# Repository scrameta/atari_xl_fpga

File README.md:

# atari_xl_fpga

An FPGA implementation of the Atari 800XL (and, with a swapped memory map, the
Atari 5200), ported to a wide range of FPGA boards. The shared core, ZPU and
common building blocks live in a separate repository,
[**atari_xl_fpga_common**](https://github.com/scrameta/atari_xl_fpga_common),
included here as a git submodule at `common/`. This repository provides the
per-board top levels, the standalone Atari chip replacements, and the firmware.

The project also grew a companion set of individual chip replacements (POKEY,
GTIA, ANTIC, Sally/6502) — one of which, **PokeyMAX**, went on to become a
product in its own right.

> This repository was migrated from a long-lived SVN history, so some of the
> commit history and layout reflects that heritage.

## Contents

- [What this is](#what-this-is)
- [Getting the code](#getting-the-code)
- [Repository layout](#repository-layout)
- [The core](#the-core)
- [Supported boards](#supported-boards)
- [Individual chip replacements](#individual-chip-replacements)
- [Downstream forks](#downstream-forks)
- [Related work](#related-work)
- [Firmware](#firmware)
- [Toolchain](#toolchain)
- [Building](#building)
- [Licensing](#licensing)
- [Credits and references](#credits-and-references)

## What this is

The project started as an Atari 800XL built on a Terasic **DE1** (Cyclone II).
Because the Atari 5200 shares most of the 800XL hardware and differs mainly in
its memory map and I/O, a 5200 variant fell out fairly naturally and is
maintained alongside the 800XL builds.

Beyond raw machine emulation, a **ZPU** soft-core provides the "glue" a real
setup needs: SIO disk-drive emulation, menu/UI, timers and similar. The ZPU and
core themselves live in the shared
[atari_xl_fpga_common](https://github.com/scrameta/atari_xl_fpga_common) repo;
the board-specific firmware builds live here in the `firmware_*` folders.

Over time the core was ported to many different FPGA boards, and separately the
individual custom Atari ICs were reimplemented as standalone RTL so they could
be dropped into real machines.

## Getting the code

The shared core is a submodule, so clone recursively:

```sh
git clone --recursive https://github.com/scrameta/atari_xl_fpga

# …or, if you already cloned without --recursive:
git submodule update --init --recursive
```

The core then appears under `common/`. To move onto a newer core revision, bump
the submodule pointer (see the
[common repo](https://github.com/scrameta/atari_xl_fpga_common#using-this-repository)
for the exact commands).

## Repository layout

Everything lives under `atari_800xl/`.

| Path | Description |
| --- | --- |
| `common/` | **Submodule:** shared core, ZPU and components — see [atari_xl_fpga_common](https://github.com/scrameta/atari_xl_fpga_common). |
| `atari_chips/` | Standalone RTL for individual Atari ICs — see [below](#individual-chip-replacements). |
| `atari_chips/hardware/` | Board designs and Gerbers for the chip-replacement hardware. |
| *(one folder per board)* | Per-board top level, pin constraints, PLLs and build scripts — see [below](#supported-boards). |
| `firmware_*` | ZPU firmware builds (see [Firmware](#firmware)). |
| `VERSION` | Core version string. |
| `buildall.sh`, `package.pl`, `makemifall` | Top-level build / packaging helpers. |

## The core

The main core lives in the `common/` submodule
([atari_xl_fpga_common](https://github.com/scrameta/atari_xl_fpga_common)) and is
shared unchanged across every board port. Each board folder in this repository
is essentially a thin top level — clocking, pin mapping, memory controller,
board-specific I/O — wrapped around that common core.

The 5200 variants (`*_5200`) reuse the same core with the 5200 memory map and
I/O differences.

## Supported boards

Each board has its own top-level folder containing its constraints, PLL/clocking
and build script.

### Actively supported / working

| Board | Folder | Notes |
| --- | --- | --- |
| Terasic DE1 | `de1`, `de1_5200` | The original target (Cyclone II). |
| MCC216 | `mcc216`, `mcc216_5200` | Arcade / retro-gaming board. |
| MCCTV | `mcctv`, `mcctv_5200` | Arcade / retro-gaming board. |
| MIST | `mist`, `mist_5200` | |
| Turbo Chameleon (v1) | `chameleon` | |
| Turbo Chameleon 2 | `chameleon2` | |
| Vampire V4 | `vampire_v4sa_atari800xl` | Pinout worked out independently. |

(`mcc_common` holds shared MCC support code.)

### Experimental / community / incomplete

| Board | Folder | Status |
| --- | --- | --- |
| FPGA Arcade Replay | `replay` | Unfinished — fought the framework and the lack of SignalTap. |
| Terasic SoCKit | `sockit` | Unfinished — DDR3 IP proved troublesome. |
| Aeon Lite | `aeon_lite` | Community-contributed board; experimental. |
| Papilio DUO | `papilioduo` | Experimental. |
| eclaireXL ITX | `eclaireXL_ITX` | |

> **Vampire V4:** the pin assignments here were reverse-engineered / worked out
> independently rather than supplied by the vendor.

## Individual chip replacements

Separately from the full-machine core, `atari_chips/` contains standalone RTL
reimplementations of the individual Atari custom ICs, intended for dropping into
real hardware. `atari_chips/hardware/` holds the associated board designs and
Gerbers, and each chip has simulation scripts and testbenches
(`simulate_*max.sh`, `tb_*max/`).

| Chip | Folder(s) | Status |
| --- | --- | --- |
| **POKEY** (PokeyMAX) | `pokey`, `pokeyv2`, `pokey_digi` | **Works — matured into a full product.** Won the ABBUC hardware competition and is actively developed as PokeyMAX. |
| **GTIA** | `gtia` | Works well; used as the author's main GTIA. Developed and working prior to Sophia. |
| **Sally (6502)** | `sally` | Works, but sees little use; HALT timing is not fully verified. |
| **ANTIC** | `antic` | Incomplete — the DMA timing was never fully nailed down. |

There is also a `digimax` (DigiMAX-style DAC) in the same area.

If you're specifically after PokeyMAX rather than the FPGA computer, that work
has taken on a life of its own — see [64kib.com](https://www.64kib.com/) and the
[ABBUC](https://www.abbuc.de/) community.

## Downstream forks

- **[Atari800_MiSTer](https://github.com/MiSTer-devel/Atari800_MiSTer)** — the
  MiSTer port. It forked this project by copying the SVN repository and has
  broadly kept the core the same, while adding newer features of its own — for
  example VBXE and PokeyMAX support integrated into the full 800XL FPGA core.
  It's actively maintained by the MiSTer community and is a good place to look
  if you want a well-supported, feature-rich build on MiSTer hardware.

## Related work

- **[tonnere](https://github.com/scrameta/tonnere)** — Project Thunder
  (*tonnere* is French for thunder), the successor board to the EclaireXL
  (itself named for lightning), now being renamed **MegaXE**. An Atari XL/XE
  FPGA board carrying this lineage forward. It shares the same
  [common core](https://github.com/scrameta/atari_xl_fpga_common).
- **`ultimate_cart`** — Veronica, a separate 65816 upgrade project for the
  800XL (not a board port of this core).

## Firmware

The ZPU firmware provides the drive emulator, menu system and supporting
services. The ZPU core and services themselves live in the `common/` submodule;
these folders hold the board-specific firmware builds:

| Folder | Description |
| --- | --- |
| `firmware_eclairexl` | Firmware for the eclaireXL / newer targets. |
| `firmware_legacy` | Firmware for the older targets. |

The build flow compiles the firmware to a ZPU ROM that is embedded into the
core (`makemif*` / `zpu_rom.*` artefacts you'll see in the board folders).

## Toolchain

Which tool you need depends on the target FPGA:

- **Altera / Intel boards** — Quartus. In general the **latest** Quartus works,
  **except** for the older Cyclone parts, which were dropped from newer
  Quartus. For those use the newest version that still supports the device:
  - **Cyclone II** (e.g. DE1): last supported by **Quartus II 13.0sp1**.
  - **Cyclone III/IV**: last supported by **Quartus II 13.1**.
  - **MAX 10** and Cyclone 10 LP: use a modern Quartus (15.x or later).
- **Xilinx boards** (Papilio DUO, Aeon Lite, FPGA Arcade Replay) — **ISE**
  (project files: `*.prj`, `*.xst`, `*.ucf`, `*.ut`). Exact ISE version isn't
  recorded; a late ISE 14.x release is the usual choice for these Spartan-6-era
  parts.

Simulation of the core and sub-blocks lives in the `common/` submodule; the
chip replacements have their own testbenches under `atari_chips/tb_*` driven by
the `simulate_*.sh` scripts. A ZPU toolchain is required to (re)build the
firmware.

## Building

Make sure the `common/` submodule is populated first (see
[Getting the code](#getting-the-code)). Each board folder then contains a
`build.sh` (and often a `build.pl`) that drives the flow for that target.
`buildall.sh` at the top level builds across boards, and `makemifall` /
`package.pl` handle ROM/MIF generation and packaging.

> This is a large, long-lived hobby codebase migrated from SVN. Build scripts
> assume the author's environment in places; expect to adjust paths and tool
> versions for your setup.

## Licensing

**Please read this carefully — the licensing here is genuinely mixed and, in
places, unsettled.**

This project combines RTL and firmware from many sources, and the shared
`common/` submodule adds more of the same. The author does **not** own copyright
in all of it, so a single blanket open-source licence (GPL or otherwise)
**cannot** be applied to the whole tree. See the `COPYRIGHT_NOTICE` file here and
the one in [atari_xl_fpga_common](https://github.com/scrameta/atari_xl_fpga_common),
which aggregate the copyright notices for the various components — note they are
acknowledged to be **incomplete**.

For the parts authored by the project author, the intent is:

> **Free to use.** If you want to use it commercially, or build significantly on
> it in a commercial product, please get in touch first.

Third-party components (e.g. the ZPU, Chameleon support code — note
`chameleon/lgpl.txt` — and other imported IP) remain under their own respective
licences, which take precedence for those files.

Because some included IP may carry redistribution or build restrictions, no
warranty is made that a complete build is free of such constraints. If you are a
rights-holder for any included component and something here is mislabelled or
shouldn't be present, please contact the author and it will be corrected.

*(This section is a description of intent, not formal legal advice, and is
expected to be tightened up over time.)*

## Credits and references

- **Author:** Mark ("nick foft" on the AtariAge forums) — <https://www.64kib.com/>
- **ABBUC** — <https://www.abbuc.de/> — where PokeyMAX won the hardware competition.
- **Phaeron (Avery Lee)** — for **Altirra** and the superb *Altirra Hardware
  Reference Manual*, an invaluable reference throughout this project:
  <https://virtualdub.org/downloads/Altirra%20Hardware%20Reference%20Manual.pdf>

### Threads and background

- Main announcement / discussion thread — *Potential new hardware*:
  <https://forums.atariage.com/topic/213827-potential-new-hardware/>
- Decap and original schematics (chip reverse-engineering reference):
  <https://forums.atariage.com/topic/223747-decap-and-original-schematics/>
- Atari 8-bit family background (Wikipedia):
  <https://en.wikipedia.org/wiki/Atari_8-bit_computers>

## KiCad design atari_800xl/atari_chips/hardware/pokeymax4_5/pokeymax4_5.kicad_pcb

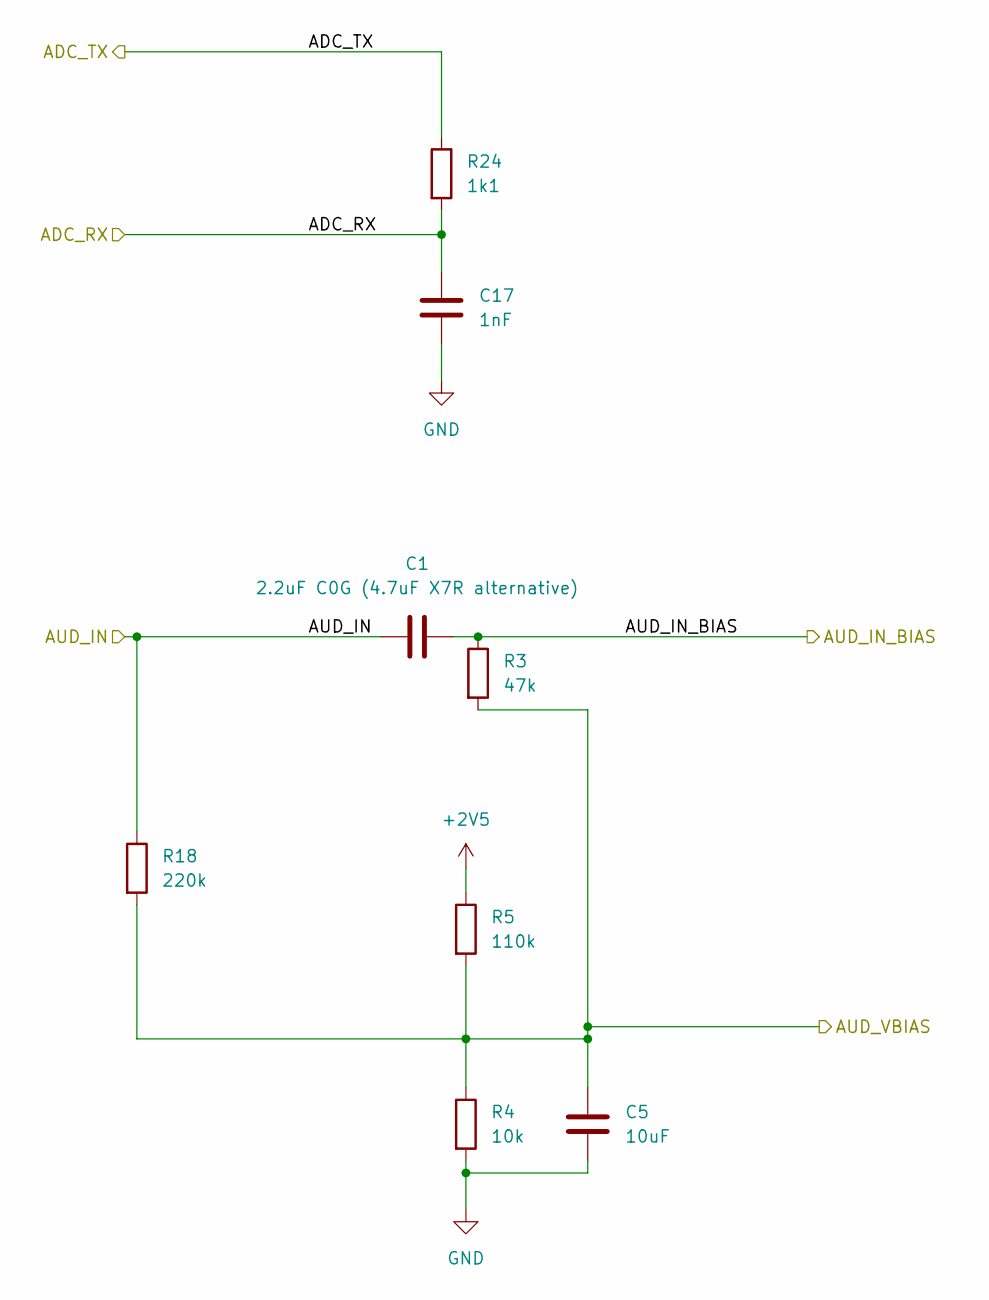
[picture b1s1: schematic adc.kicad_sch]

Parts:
C1: 2.2uF C0G (4.7uF X7R alternative); C_0603_1608Metric; LCSC C5360844
C5: 10uF; C_0603_1608Metric; LCSC C19702
C17: 1nF; C_0402_1005Metric; LCSC C126493
R3: 47k; R_0603_1608Metric; LCSC C25819
R4: 10k; R_0603_1608Metric; LCSC C25804
R5: 110k; R_0603_1608Metric; LCSC C137807
R18: 220k; R_0603_1608Metric; LCSC C22961
R24: 1k1; R_0402_1005Metric; LCSC C25860

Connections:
+2V5: R5.1; also elsewhere on the board
/ADC/ADC_RX: C17.1, R24.2; also elsewhere on the board
/ADC/ADC_TX: R24.1; also elsewhere on the board
/ADC/AUD_IN: C1.1, R18.1; also elsewhere on the board
/ADC/AUD_IN_BIAS: C1.2, R3.1; also elsewhere on the board
/ADC/AUD_VBIAS: C5.2, R3.2, R4.1, R5.2, R18.2; also elsewhere on the board
GND: C5.1, C17.2, R4.2; also elsewhere on the board

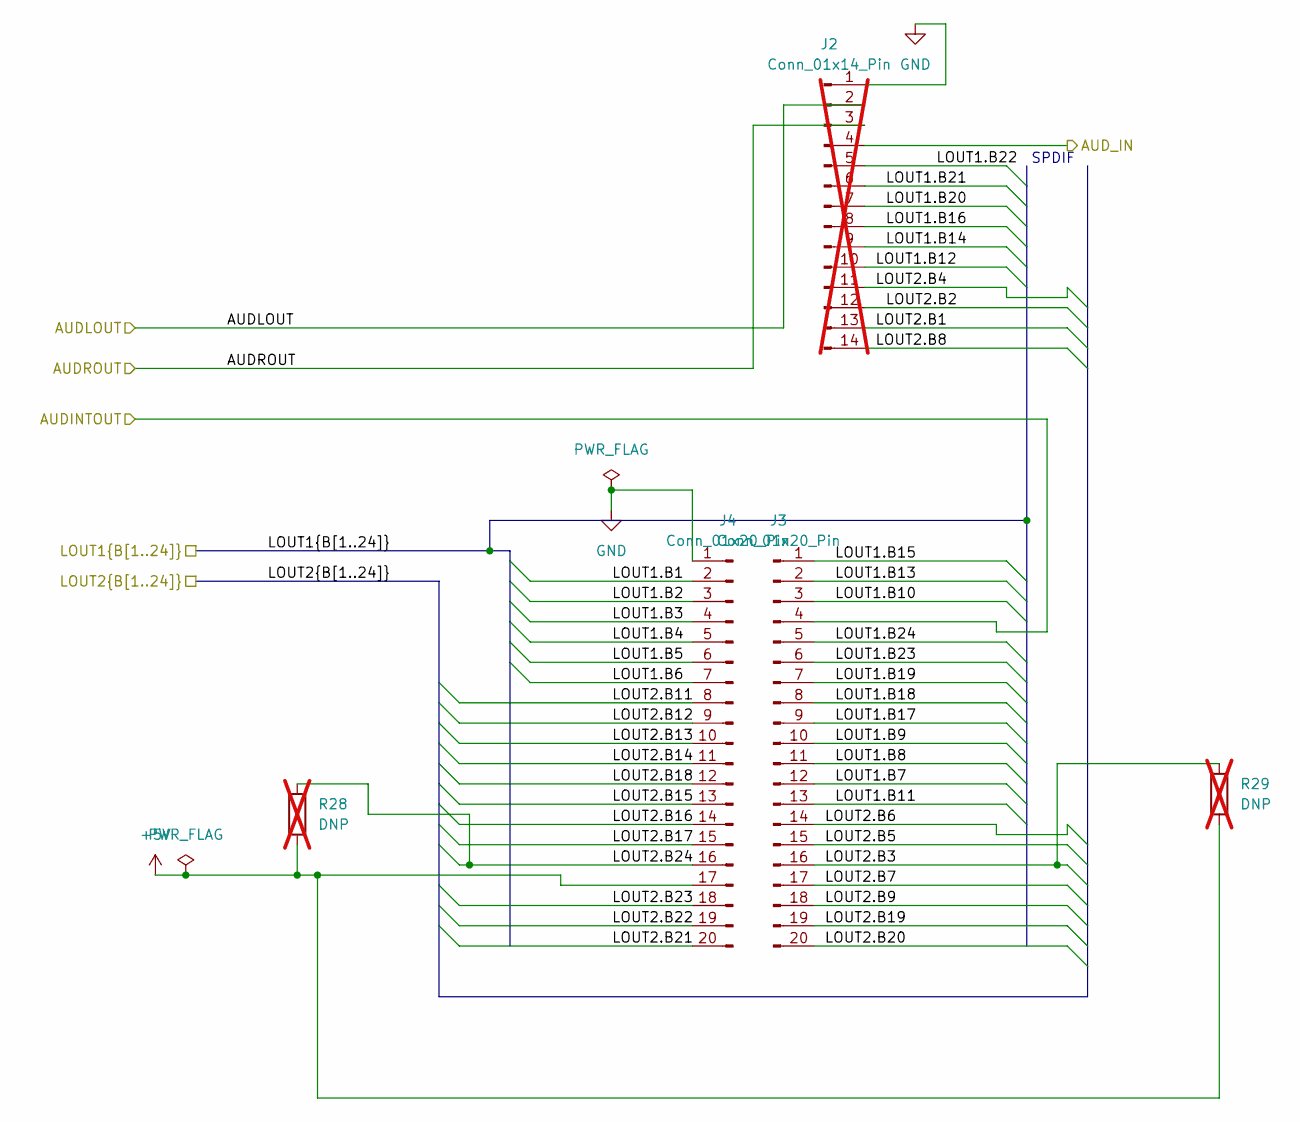
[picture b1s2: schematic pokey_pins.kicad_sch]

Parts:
J2: Conn_01x14_Pin; PinHeader_1x14_P2.54mm_Vertical; not fitted
J3, J4: Conn_01x20_Pin; PinSocket_1x20_P2.54mm_Vertical; LCSC C5156447
R28, R29: DNP; R_0603_1608Metric; not fitted

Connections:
+5V: J4.17, R28.2, R29.2; also elsewhere on the board
/ADC/AUD_IN: J2.4; also elsewhere on the board
/Audio output/AUDLOUT: J2.2; also elsewhere on the board
/Audio output/AUDROUT: J2.3; also elsewhere on the board
/Audio output/AUD_INT_OUT: J3.4; also elsewhere on the board
/Level shifter/LOUT1.B1: J4.2; also elsewhere on the board
/Level shifter/LOUT1.B2: J4.3; also elsewhere on the board
/Level shifter/LOUT1.B3: J4.4; also elsewhere on the board
/Level shifter/LOUT1.B4: J4.5; also elsewhere on the board
/Level shifter/LOUT1.B5: J4.6; also elsewhere on the board
/Level shifter/LOUT1.B6: J4.7; also elsewhere on the board
/Level shifter/LOUT1.B7: J3.12; also elsewhere on the board
/Level shifter/LOUT1.B8: J3.11; also elsewhere on the board
/Level shifter/LOUT1.B9: J3.10; also elsewhere on the board
/Level shifter/LOUT1.B10: J3.3; also elsewhere on the board
/Level shifter/LOUT1.B11: J3.13; also elsewhere on the board
/Level shifter/LOUT1.B12: J2.10; also elsewhere on the board
/Level shifter/LOUT1.B13: J3.2; also elsewhere on the board
/Level shifter/LOUT1.B14: J2.9; also elsewhere on the board
/Level shifter/LOUT1.B15: J3.1; also elsewhere on the board
/Level shifter/LOUT1.B16: J2.8; also elsewhere on the board
/Level shifter/LOUT1.B17: J3.9; also elsewhere on the board
/Level shifter/LOUT1.B18: J3.8; also elsewhere on the board
/Level shifter/LOUT1.B19: J3.7; also elsewhere on the board
/Level shifter/LOUT1.B20: J2.7; also elsewhere on the board
/Level shifter/LOUT1.B21: J2.6; also elsewhere on the board
/Level shifter/LOUT1.B22: J2.5; also elsewhere on the board
/Level shifter/LOUT1.B23: J3.6; also elsewhere on the board
/Level shifter/LOUT1.B24: J3.5; also elsewhere on the board
/Level shifter/LOUT2.B1: J2.13; also elsewhere on the board
/Level shifter/LOUT2.B2: J2.12; also elsewhere on the board
/Level shifter/LOUT2.B3: J3.16, R29.1; also elsewhere on the board
/Level shifter/LOUT2.B4: J2.11; also elsewhere on the board
/Level shifter/LOUT2.B5: J3.15; also elsewhere on the board
/Level shifter/LOUT2.B6: J3.14; also elsewhere on the board
/Level shifter/LOUT2.B7: J3.17; also elsewhere on the board
/Level shifter/LOUT2.B8: J2.14; also elsewhere on the board
/Level shifter/LOUT2.B9: J3.18; also elsewhere on the board
/Level shifter/LOUT2.B11: J4.8; also elsewhere on the board
/Level shifter/LOUT2.B12: J4.9; also elsewhere on the board
/Level shifter/LOUT2.B13: J4.10; also elsewhere on the board
/Level shifter/LOUT2.B14: J4.11; also elsewhere on the board
/Level shifter/LOUT2.B15: J4.13; also elsewhere on the board
/Level shifter/LOUT2.B16: J4.14; also elsewhere on the board
/Level shifter/LOUT2.B17: J4.15; also elsewhere on the board
/Level shifter/LOUT2.B18: J4.12; also elsewhere on the board
/Level shifter/LOUT2.B19: J3.19; also elsewhere on the board
/Level shifter/LOUT2.B20: J3.20; also elsewhere on the board
/Level shifter/LOUT2.B21: J4.20; also elsewhere on the board
/Level shifter/LOUT2.B22: J4.19; also elsewhere on the board
/Level shifter/LOUT2.B23: J4.18; also elsewhere on the board
/Level shifter/LOUT2.B24: J4.16, R28.1; also elsewhere on the board
GND: J2.1, J4.1; also elsewhere on the board

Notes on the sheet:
SPDIF

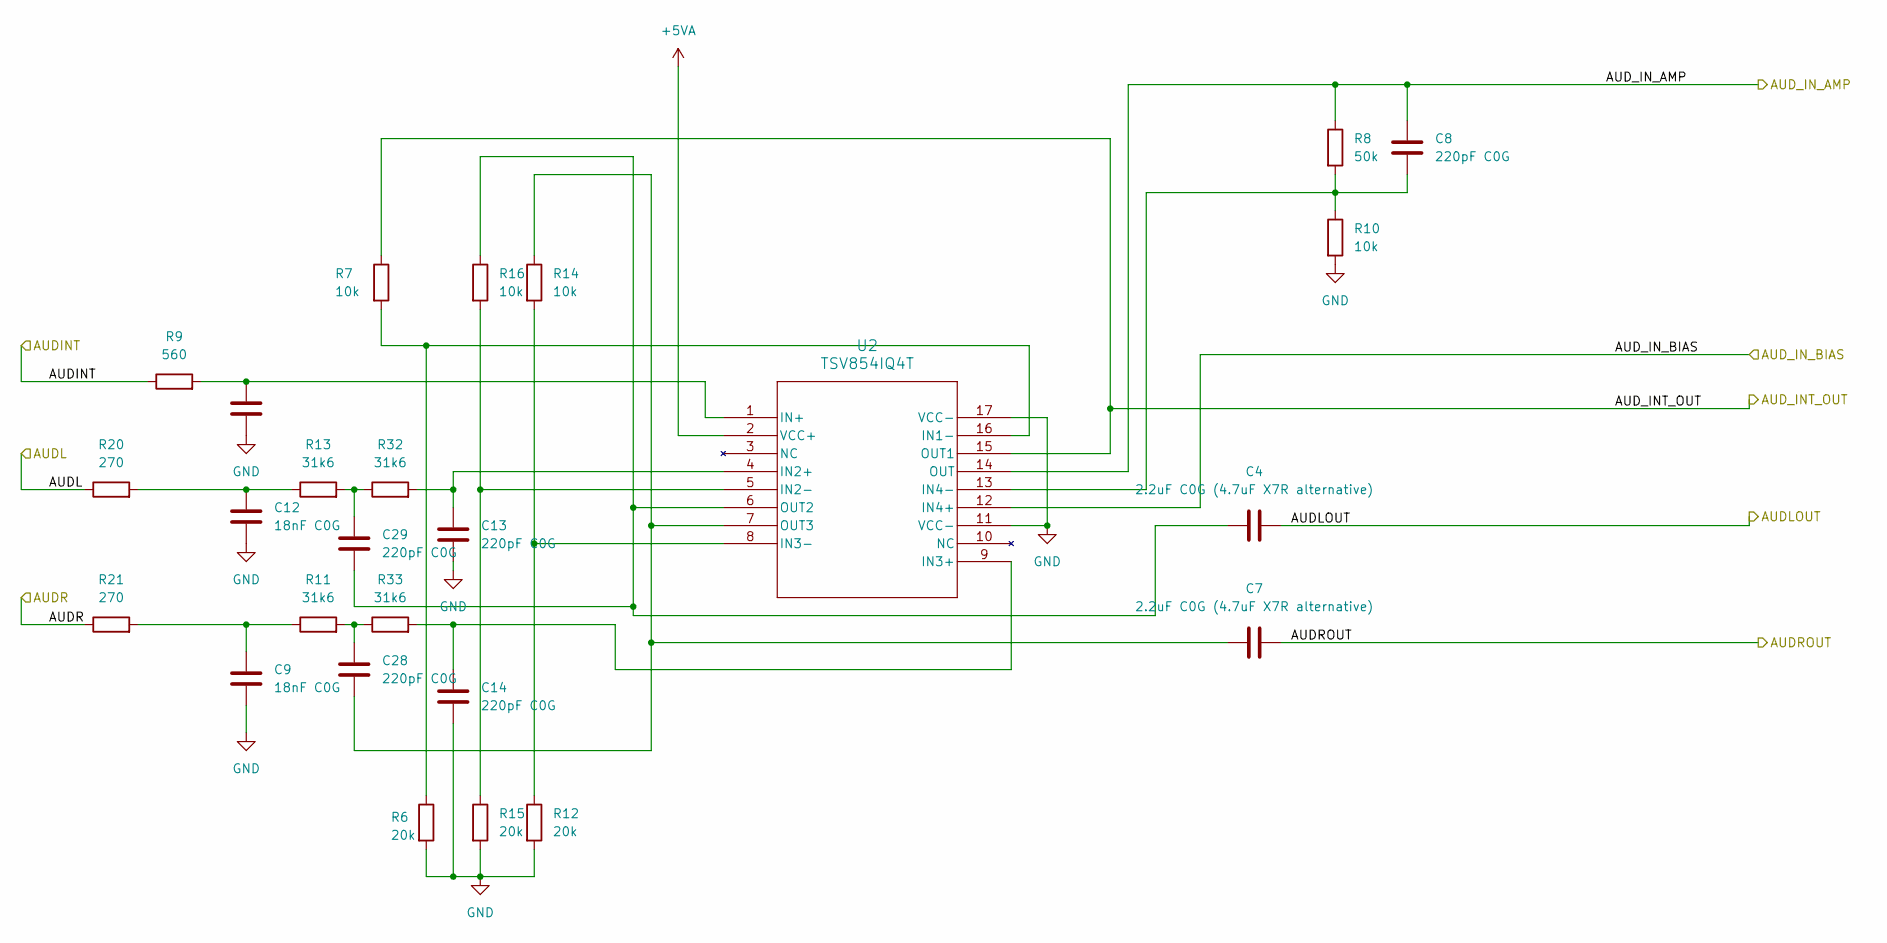
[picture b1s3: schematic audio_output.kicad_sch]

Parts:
C4, C7: 2.2uF C0G (4.7uF X7R alternative); C_0603_1608Metric; LCSC C5360844
C6, C9, C12: 18nF C0G; C_0402_1005Metric; LCSC C710669
C8, C13, C14, C28, C29: 220pF C0G; C_0402_1005Metric; LCSC C71693
R6, R12, R15: 20k; R_0402_1005Metric; LCSC C25765
R7, R10, R14, R16: 10k; R_0402_1005Metric; LCSC C25744
R8: 50k; R_0402_1005Metric; LCSC C166559
R9: 560; R_0402_1005Metric; LCSC C163460
R11, R13, R32, R33: 31k6; R_0402_1005Metric; LCSC C11463
R20, R21: 270; R_0402_1005Metric; LCSC C163474
U2: TSV854IQ4T; QFN16_3X3_STM; LCSC C2058240

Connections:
+5VA: U2.2 (VCC+); also elsewhere on the board
/ADC/AUD_IN_BIAS: U2.12 (IN4+); also elsewhere on the board
/Audio output/AUDINT: R9.1; also elsewhere on the board
/Audio output/AUDL: R20.1; also elsewhere on the board
/Audio output/AUDLOUT: C4.2; also elsewhere on the board
/Audio output/AUDR: R21.1; also elsewhere on the board
/Audio output/AUDROUT: C7.2; also elsewhere on the board
/Audio output/AUD_INT_OUT: R7.1, U2.15 (OUT1); also elsewhere on the board
/Audio output/AUD_IN_AMP: C8.1, R8.1, U2.14 (OUT); also elsewhere on the board
GND: C6.2, C9.2, C12.2, C13.2, C14.2, R6.2, R10.2, R12.2, R15.2, U2.11 (VCC-), U2.17 (VCC-); also elsewhere on the board
unnamed: C9.1, R11.1, R21.2
unnamed: C12.1, R13.1, R20.2
unnamed: C28.1, R11.2, R33.1
unnamed: C29.1, R13.2, R32.1
unnamed: R6.1, R7.2, U2.16 (IN1-)
unnamed: C13.1, R32.2, U2.4 (IN2+)
unnamed: R15.1, R16.2, U2.5 (IN2-)
unnamed: C14.1, R33.2, U2.9 (IN3+)
unnamed: R12.1, R14.2, U2.8 (IN3-)
unnamed: C8.2, R8.2, R10.1, U2.13 (IN4-)
unnamed: C6.1, R9.2, U2.1 (IN+)
unnamed: C4.1, C29.2, R16.1, U2.6 (OUT2)
unnamed: C7.1, C28.2, R14.1, U2.7 (OUT3)

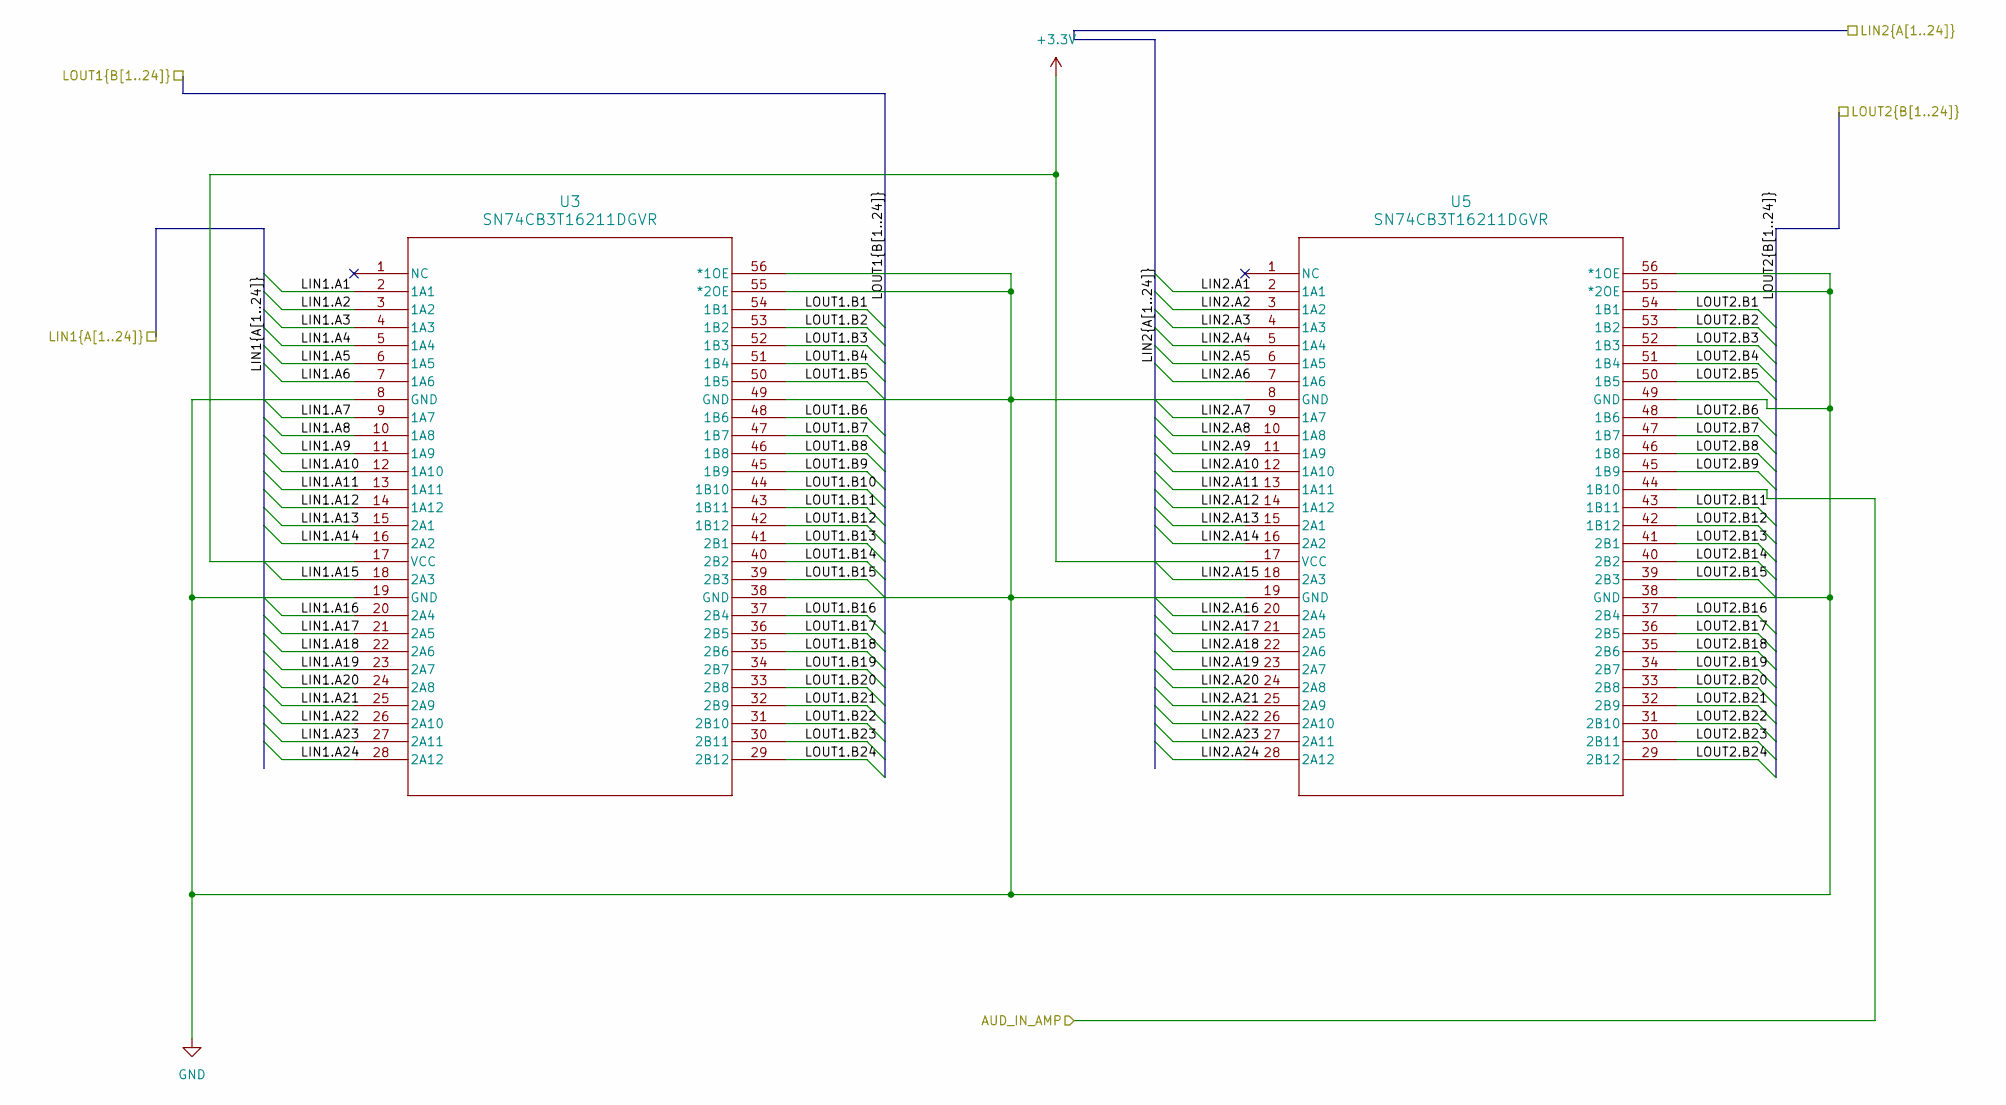
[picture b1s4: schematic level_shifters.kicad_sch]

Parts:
U3, U5: SN74CB3T16211DGVR; DGV56-L; LCSC C2674751

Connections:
+3.3V: U3.17 (VCC), U5.17 (VCC); also elsewhere on the board
/Audio output/AUD_IN_AMP: U5.44 (1B10); also elsewhere on the board
/FPGA/LIN1.A1: U3.2 (1A1); also elsewhere on the board
/FPGA/LIN1.A2: U3.3 (1A2); also elsewhere on the board
/FPGA/LIN1.A3: U3.4 (1A3); also elsewhere on the board
/FPGA/LIN1.A4: U3.5 (1A4); also elsewhere on the board
/FPGA/LIN1.A5: U3.6 (1A5); also elsewhere on the board
/FPGA/LIN1.A6: U3.7 (1A6); also elsewhere on the board
/FPGA/LIN1.A7: U3.9 (1A7); also elsewhere on the board
/FPGA/LIN1.A8: U3.10 (1A8); also elsewhere on the board
/FPGA/LIN1.A9: U3.11 (1A9); also elsewhere on the board
/FPGA/LIN1.A10: U3.12 (1A10); also elsewhere on the board
/FPGA/LIN1.A11: U3.13 (1A11); also elsewhere on the board
/FPGA/LIN1.A12: U3.14 (1A12); also elsewhere on the board
/FPGA/LIN1.A13: U3.15 (2A1); also elsewhere on the board
/FPGA/LIN1.A14: U3.16 (2A2); also elsewhere on the board
/FPGA/LIN1.A15: U3.18 (2A3); also elsewhere on the board
/FPGA/LIN1.A16: U3.20 (2A4); also elsewhere on the board
/FPGA/LIN1.A17: U3.21 (2A5); also elsewhere on the board
/FPGA/LIN1.A18: U3.22 (2A6); also elsewhere on the board
/FPGA/LIN1.A19: U3.23 (2A7); also elsewhere on the board
/FPGA/LIN1.A20: U3.24 (2A8); also elsewhere on the board
/FPGA/LIN1.A21: U3.25 (2A9); also elsewhere on the board
/FPGA/LIN1.A22: U3.26 (2A10); also elsewhere on the board
/FPGA/LIN1.A23: U3.27 (2A11); also elsewhere on the board
/FPGA/LIN1.A24: U3.28 (2A12); also elsewhere on the board
/FPGA/LIN2.A1: U5.2 (1A1); also elsewhere on the board
/FPGA/LIN2.A2: U5.3 (1A2); also elsewhere on the board
/FPGA/LIN2.A3: U5.4 (1A3); also elsewhere on the board
/FPGA/LIN2.A4: U5.5 (1A4); also elsewhere on the board
/FPGA/LIN2.A5: U5.6 (1A5); also elsewhere on the board
/FPGA/LIN2.A6: U5.7 (1A6); also elsewhere on the board
/FPGA/LIN2.A7: U5.9 (1A7); also elsewhere on the board
/FPGA/LIN2.A8: U5.10 (1A8); also elsewhere on the board
/FPGA/LIN2.A9: U5.11 (1A9); also elsewhere on the board
/FPGA/LIN2.A10: U5.12 (1A10); also elsewhere on the board
/FPGA/LIN2.A11: U5.13 (1A11); also elsewhere on the board
/FPGA/LIN2.A12: U5.14 (1A12); also elsewhere on the board
/FPGA/LIN2.A13: U5.15 (2A1); also elsewhere on the board
/FPGA/LIN2.A14: U5.16 (2A2); also elsewhere on the board
/FPGA/LIN2.A15: U5.18 (2A3); also elsewhere on the board
/FPGA/LIN2.A16: U5.20 (2A4); also elsewhere on the board
/FPGA/LIN2.A17: U5.21 (2A5); also elsewhere on the board
/FPGA/LIN2.A18: U5.22 (2A6); also elsewhere on the board
/FPGA/LIN2.A19: U5.23 (2A7); also elsewhere on the board
/FPGA/LIN2.A20: U5.24 (2A8); also elsewhere on the board
/FPGA/LIN2.A21: U5.25 (2A9); also elsewhere on the board
/FPGA/LIN2.A22: U5.26 (2A10); also elsewhere on the board
/FPGA/LIN2.A23: U5.27 (2A11); also elsewhere on the board
/FPGA/LIN2.A24: U5.28 (2A12); also elsewhere on the board
/Level shifter/LOUT1.B1: U3.54 (1B1); also elsewhere on the board
/Level shifter/LOUT1.B2: U3.53 (1B2); also elsewhere on the board
/Level shifter/LOUT1.B3: U3.52 (1B3); also elsewhere on the board
/Level shifter/LOUT1.B4: U3.51 (1B4); also elsewhere on the board
/Level shifter/LOUT1.B5: U3.50 (1B5); also elsewhere on the board
/Level shifter/LOUT1.B6: U3.48 (1B6); also elsewhere on the board
/Level shifter/LOUT1.B7: U3.47 (1B7); also elsewhere on the board
/Level shifter/LOUT1.B8: U3.46 (1B8); also elsewhere on the board
/Level shifter/LOUT1.B9: U3.45 (1B9); also elsewhere on the board
/Level shifter/LOUT1.B10: U3.44 (1B10); also elsewhere on the board
/Level shifter/LOUT1.B11: U3.43 (1B11); also elsewhere on the board
/Level shifter/LOUT1.B12: U3.42 (1B12); also elsewhere on the board
/Level shifter/LOUT1.B13: U3.41 (2B1); also elsewhere on the board
/Level shifter/LOUT1.B14: U3.40 (2B2); also elsewhere on the board
/Level shifter/LOUT1.B15: U3.39 (2B3); also elsewhere on the board
/Level shifter/LOUT1.B16: U3.37 (2B4); also elsewhere on the board
/Level shifter/LOUT1.B17: U3.36 (2B5); also elsewhere on the board
/Level shifter/LOUT1.B18: U3.35 (2B6); also elsewhere on the board
/Level shifter/LOUT1.B19: U3.34 (2B7); also elsewhere on the board
/Level shifter/LOUT1.B20: U3.33 (2B8); also elsewhere on the board
/Level shifter/LOUT1.B21: U3.32 (2B9); also elsewhere on the board
/Level shifter/LOUT1.B22: U3.31 (2B10); also elsewhere on the board
/Level shifter/LOUT1.B23: U3.30 (2B11); also elsewhere on the board
/Level shifter/LOUT1.B24: U3.29 (2B12); also elsewhere on the board
/Level shifter/LOUT2.B1: U5.54 (1B1); also elsewhere on the board
/Level shifter/LOUT2.B2: U5.53 (1B2); also elsewhere on the board
/Level shifter/LOUT2.B3: U5.52 (1B3); also elsewhere on the board
/Level shifter/LOUT2.B4: U5.51 (1B4); also elsewhere on the board
/Level shifter/LOUT2.B5: U5.50 (1B5); also elsewhere on the board
/Level shifter/LOUT2.B6: U5.48 (1B6); also elsewhere on the board
/Level shifter/LOUT2.B7: U5.47 (1B7); also elsewhere on the board
/Level shifter/LOUT2.B8: U5.46 (1B8); also elsewhere on the board
/Level shifter/LOUT2.B9: U5.45 (1B9); also elsewhere on the board
/Level shifter/LOUT2.B11: U5.43 (1B11); also elsewhere on the board
/Level shifter/LOUT2.B12: U5.42 (1B12); also elsewhere on the board
/Level shifter/LOUT2.B13: U5.41 (2B1); also elsewhere on the board
/Level shifter/LOUT2.B14: U5.40 (2B2); also elsewhere on the board
/Level shifter/LOUT2.B15: U5.39 (2B3); also elsewhere on the board
/Level shifter/LOUT2.B16: U5.37 (2B4); also elsewhere on the board
/Level shifter/LOUT2.B17: U5.36 (2B5); also elsewhere on the board
/Level shifter/LOUT2.B18: U5.35 (2B6); also elsewhere on the board
/Level shifter/LOUT2.B19: U5.34 (2B7); also elsewhere on the board
/Level shifter/LOUT2.B20: U5.33 (2B8); also elsewhere on the board
/Level shifter/LOUT2.B21: U5.32 (2B9); also elsewhere on the board
/Level shifter/LOUT2.B22: U5.31 (2B10); also elsewhere on the board
/Level shifter/LOUT2.B23: U5.30 (2B11); also elsewhere on the board
/Level shifter/LOUT2.B24: U5.29 (2B12); also elsewhere on the board
GND: U3.8 (GND), U3.19 (GND), U3.38 (GND), U3.49 (GND), U3.55 (*2OE), U3.56 (*1OE), U5.8 (GND), U5.19 (GND), U5.38 (GND), U5.49 (GND), U5.55 (*2OE), U5.56 (*1OE); also elsewhere on the board

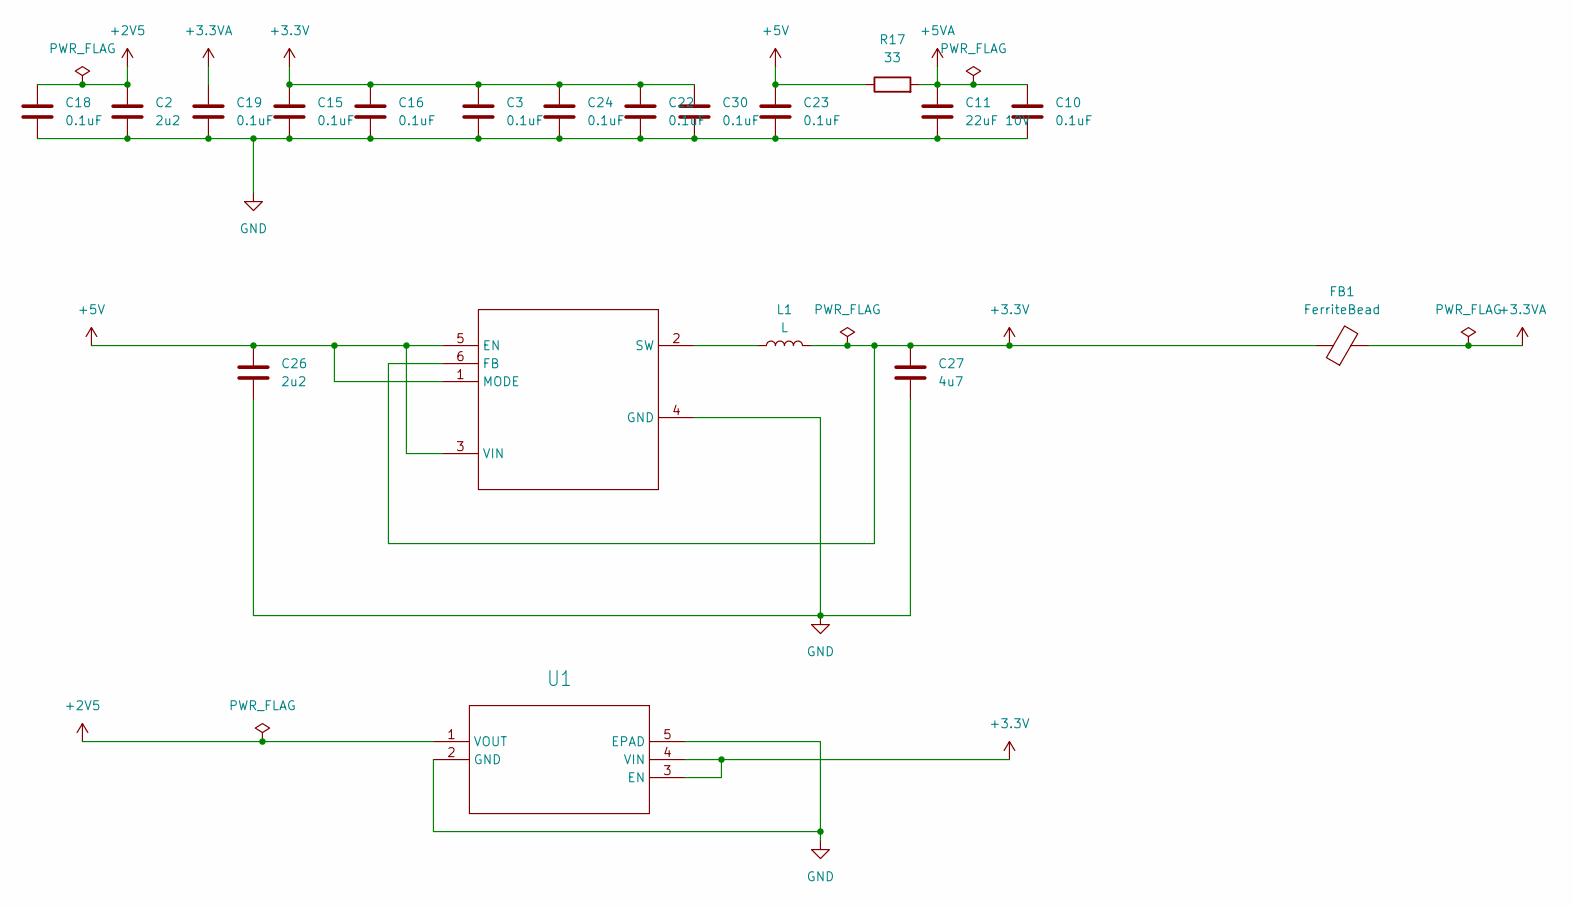
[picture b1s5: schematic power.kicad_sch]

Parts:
C2, C26: 2u2; C_0603_1608Metric; LCSC C23630
C3, C15, C16, C18, C19, C22, C23, C24: 0.1uF; C_0603_1608Metric; LCSC C14663
C10: 0.1uF; C_0402_1005Metric; LCSC C1525
C11: 22uF 10V; C_0603_1608Metric; LCSC C86295
C27: 4u7; C_0603_1608Metric; LCSC C19666
C30: 0.1uF; C_0402_1005Metric; LCSC C14663
FB1: FerriteBead; L_0603_1608Metric; LCSC C19330
L1: L; L_1008_2520Metric_Pad1.43x2.20mm_HandSolder; LCSC C171753
R17: 33; R_0603_1608Metric; LCSC C23140
U1: TDFN4_1P2X1P6_MCH; LCSC C622555
U6: DRY6; LCSC C398923

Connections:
+2V5: C2.1, C18.1, U1.1 (VOUT); also elsewhere on the board
+3.3V: C3.1, C15.1, C16.1, C22.1, C24.1, C27.1, C30.1, FB1.1, L1.2, U1.3 (EN), U1.4 (VIN), U6.6 (FB); also elsewhere on the board
+3.3VA: C19.1, FB1.2; also elsewhere on the board
+5V: C23.1, C26.1, R17.1, U6.1 (MODE), U6.3 (VIN), U6.5 (EN); also elsewhere on the board
+5VA: C10.1, C11.1, R17.2; also elsewhere on the board
GND: C2.2, C3.2, C10.2, C11.2, C15.2, C16.2, C18.2, C19.2, C22.2, C23.2, C24.2, C26.2, C27.2, C30.2, U1.2 (GND), U1.5 (EPAD), U6.4 (GND); also elsewhere on the board
unnamed: L1.1, U6.2 (SW)

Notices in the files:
atari_800xl/atari_chips/pokeyv2/pokeymaxv2.qsf:
Copyright (C) 2017  Intel Corporation. All rights reserved.
atari_800xl/eclaireXL_ITX/atari800core_eclaireXLv1.qsf:
Copyright (C) 1991-2014 Altera Corporation. All rights reserved.
atari_800xl/eclaireXL_ITX/hardware/kicad_project/main/eclaireXLv1.kicad_pcb:
(c)2016 by Mark Watson
